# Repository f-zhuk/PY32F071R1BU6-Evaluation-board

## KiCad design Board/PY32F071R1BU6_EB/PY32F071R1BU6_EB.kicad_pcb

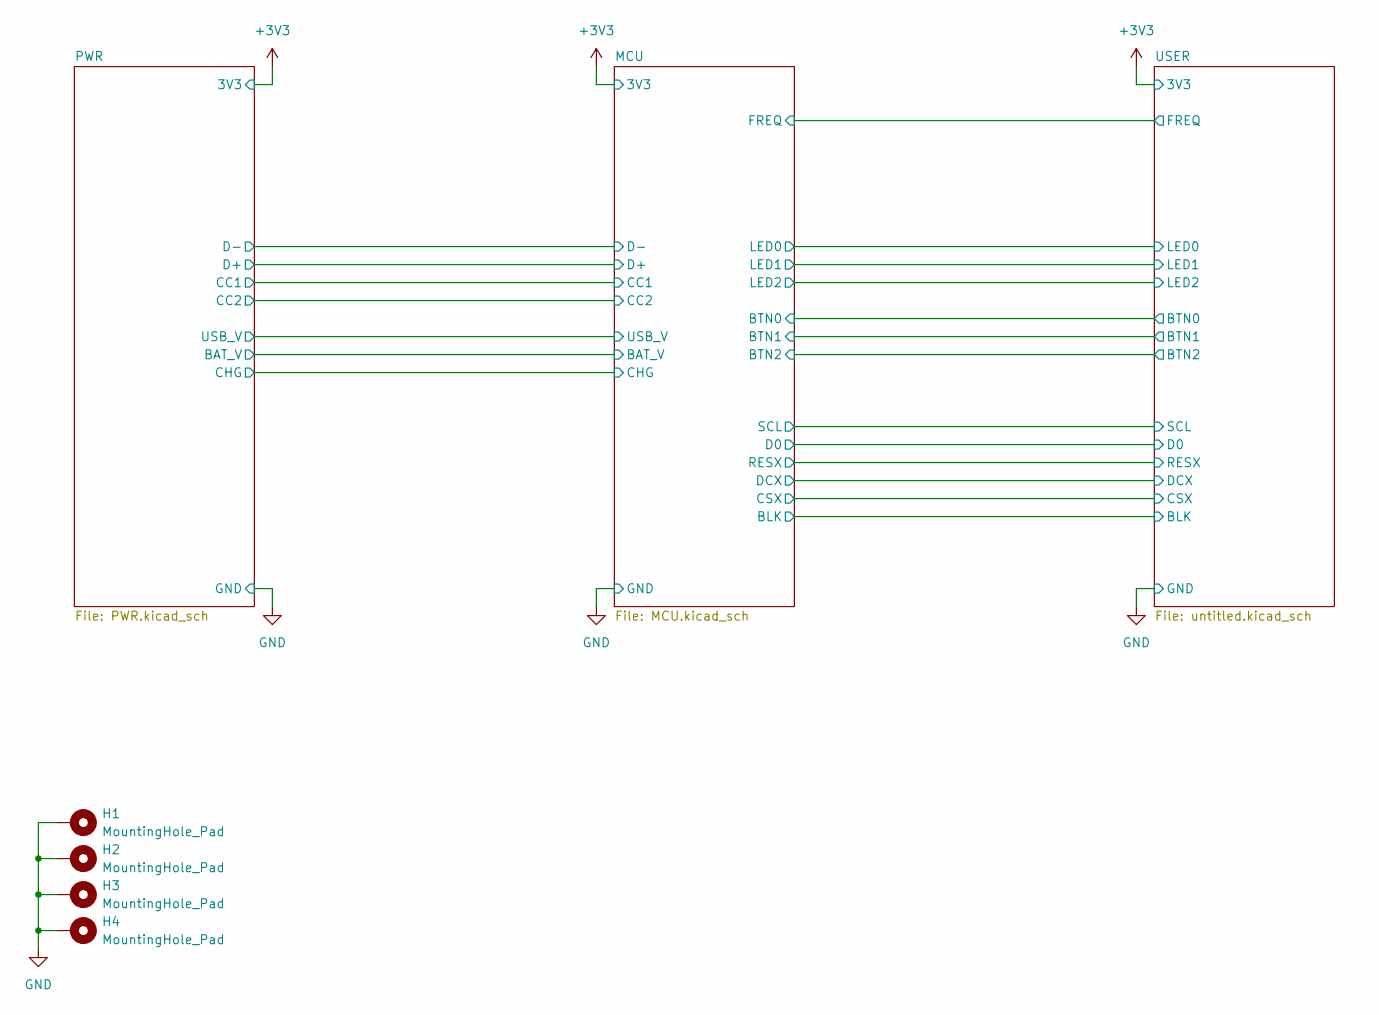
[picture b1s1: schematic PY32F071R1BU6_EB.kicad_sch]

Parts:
H1, H2, H3, H4: MountingHole_Pad; MountingHole_4.3mm_M4_Pad

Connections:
GND: H1.1, H2.1, H3.1, H4.1; also elsewhere on the board

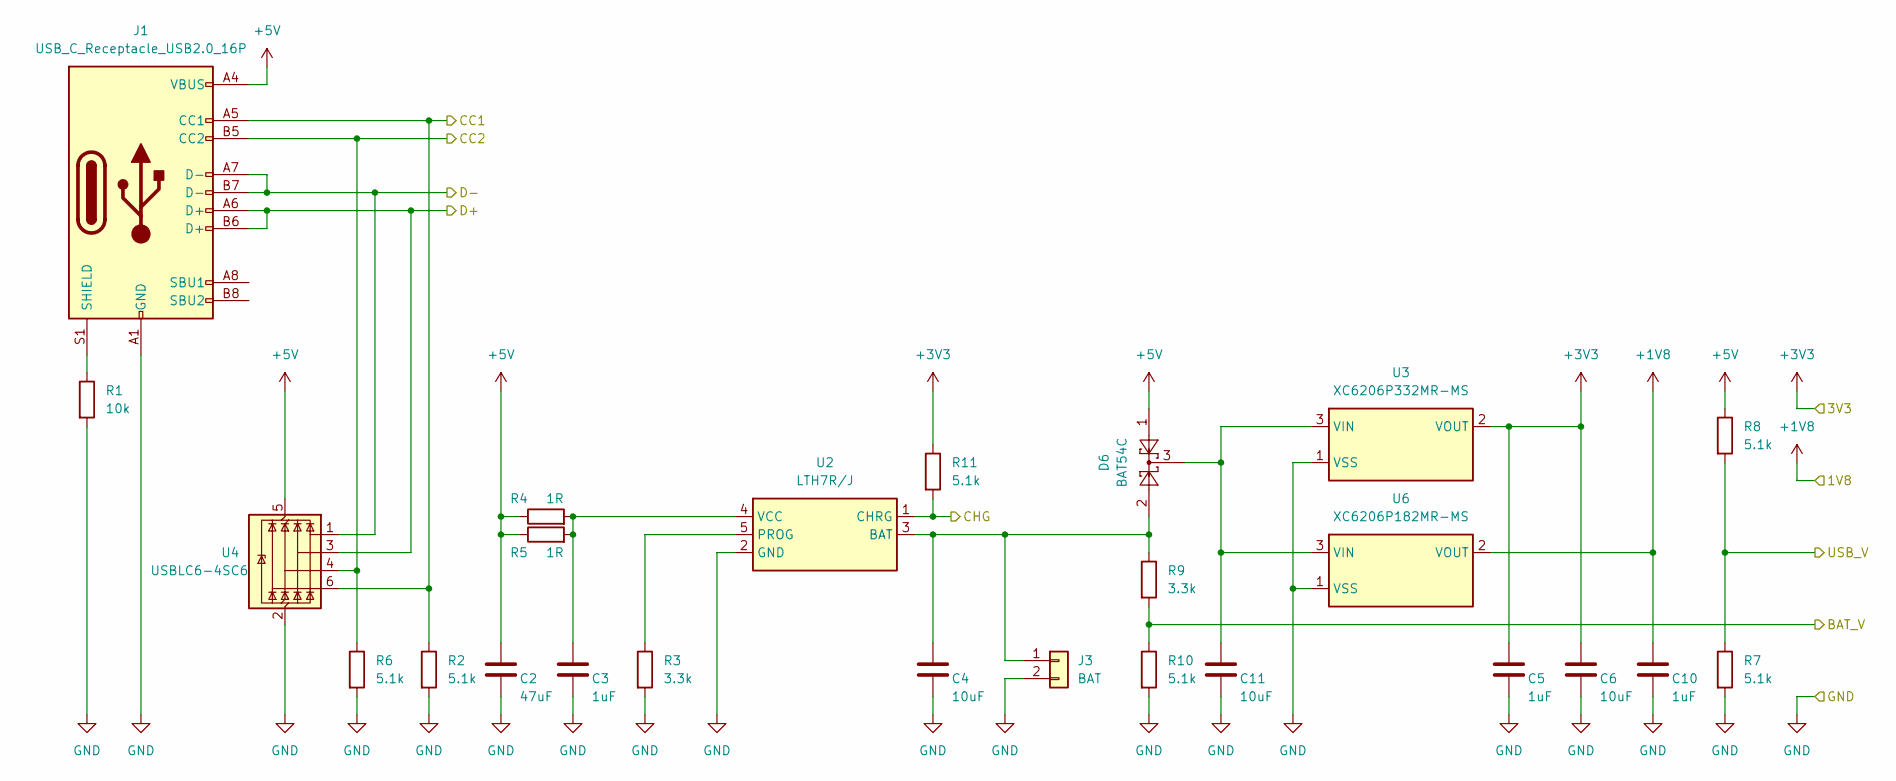
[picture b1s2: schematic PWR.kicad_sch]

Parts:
C2: 47uF; C_0805_2012Metric_Pad1.18x1.45mm_HandSolder; Voltage 10V
C3, C5, C10: 1uF; C_0603_1608Metric_Pad1.08x0.95mm_HandSolder; Voltage 10V
C4, C6, C11: 10uF; C_0603_1608Metric_Pad1.08x0.95mm_HandSolder; Voltage 10V
D6: BAT54C; SOT-23-3
J1: USB_C_Receptacle_USB2.0_16P; USB_C_Receptacle_HCTL_HC-TYPE-C-16P-01A
J3: BAT; PinHeader_1x02_P2.54mm_Vertical
R1: 10k; R_0603_1608Metric_Pad0.98x0.95mm_HandSolder
R2, R6, R7, R8, R10, R11: 5.1k; R_0603_1608Metric_Pad0.98x0.95mm_HandSolder
R3, R9: 3.3k; R_0603_1608Metric_Pad0.98x0.95mm_HandSolder
R4, R5: 1R; R_0603_1608Metric_Pad0.98x0.95mm_HandSolder
U2: LTH7R/J; SOT-23-5
U3: XC6206P332MR-MS; SOT-23-3
U4: USBLC6-4SC6; SOT-23-6
U6: XC6206P182MR-MS; SOT-23-3

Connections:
+1V8: C10.1, U6.2 (VOUT)
+3V3: C5.1, C6.1, R11.1, U3.2 (VOUT); also elsewhere on the board
+5V: C2.1, D6.1, J1.A4 (VBUS), J1.A9 (VBUS), J1.B4 (VBUS), J1.B9 (VBUS), R4.1, R5.1, R8.1, U4.5 (VBUS); also elsewhere on the board
/MCU/BAT_V: R9.2, R10.1; also elsewhere on the board
/MCU/CC1: J1.A5 (CC1), R2.1, U4.6 (I/O4); also elsewhere on the board
/MCU/CC2: J1.B5 (CC2), R6.1, U4.4 (I/O3); also elsewhere on the board
/MCU/CHG: R11.2, U2.1 (CHRG); also elsewhere on the board
/MCU/D+: J1.A6 (D+), J1.B6 (D+), U4.3 (I/O2); also elsewhere on the board
/MCU/D-: J1.A7 (D-), J1.B7 (D-), U4.1 (I/O1); also elsewhere on the board
/MCU/USB_V: R7.1, R8.2; also elsewhere on the board
GND: C2.2, C3.2, C4.2, C5.2, C6.2, C10.2, C11.2, J1.A1 (GND), J1.A12 (GND), J1.B1 (GND), J1.B12 (GND), J3.2, R1.2, R2.2, R3.2, R6.2, R7.2, R10.2, U2.2 (GND), U3.1 (VSS), U4.2 (GND), U6.1 (VSS); also elsewhere on the board
unnamed: J1.S1 (SHIELD), R1.1
unnamed: C4.1, D6.2, J3.1, R9.1, U2.3 (BAT)
unnamed: R3.1, U2.5 (PROG)
unnamed: C3.1, R4.2, R5.2, U2.4 (VCC)
unnamed: C11.1, D6.3, U3.3 (VIN), U6.3 (VIN)

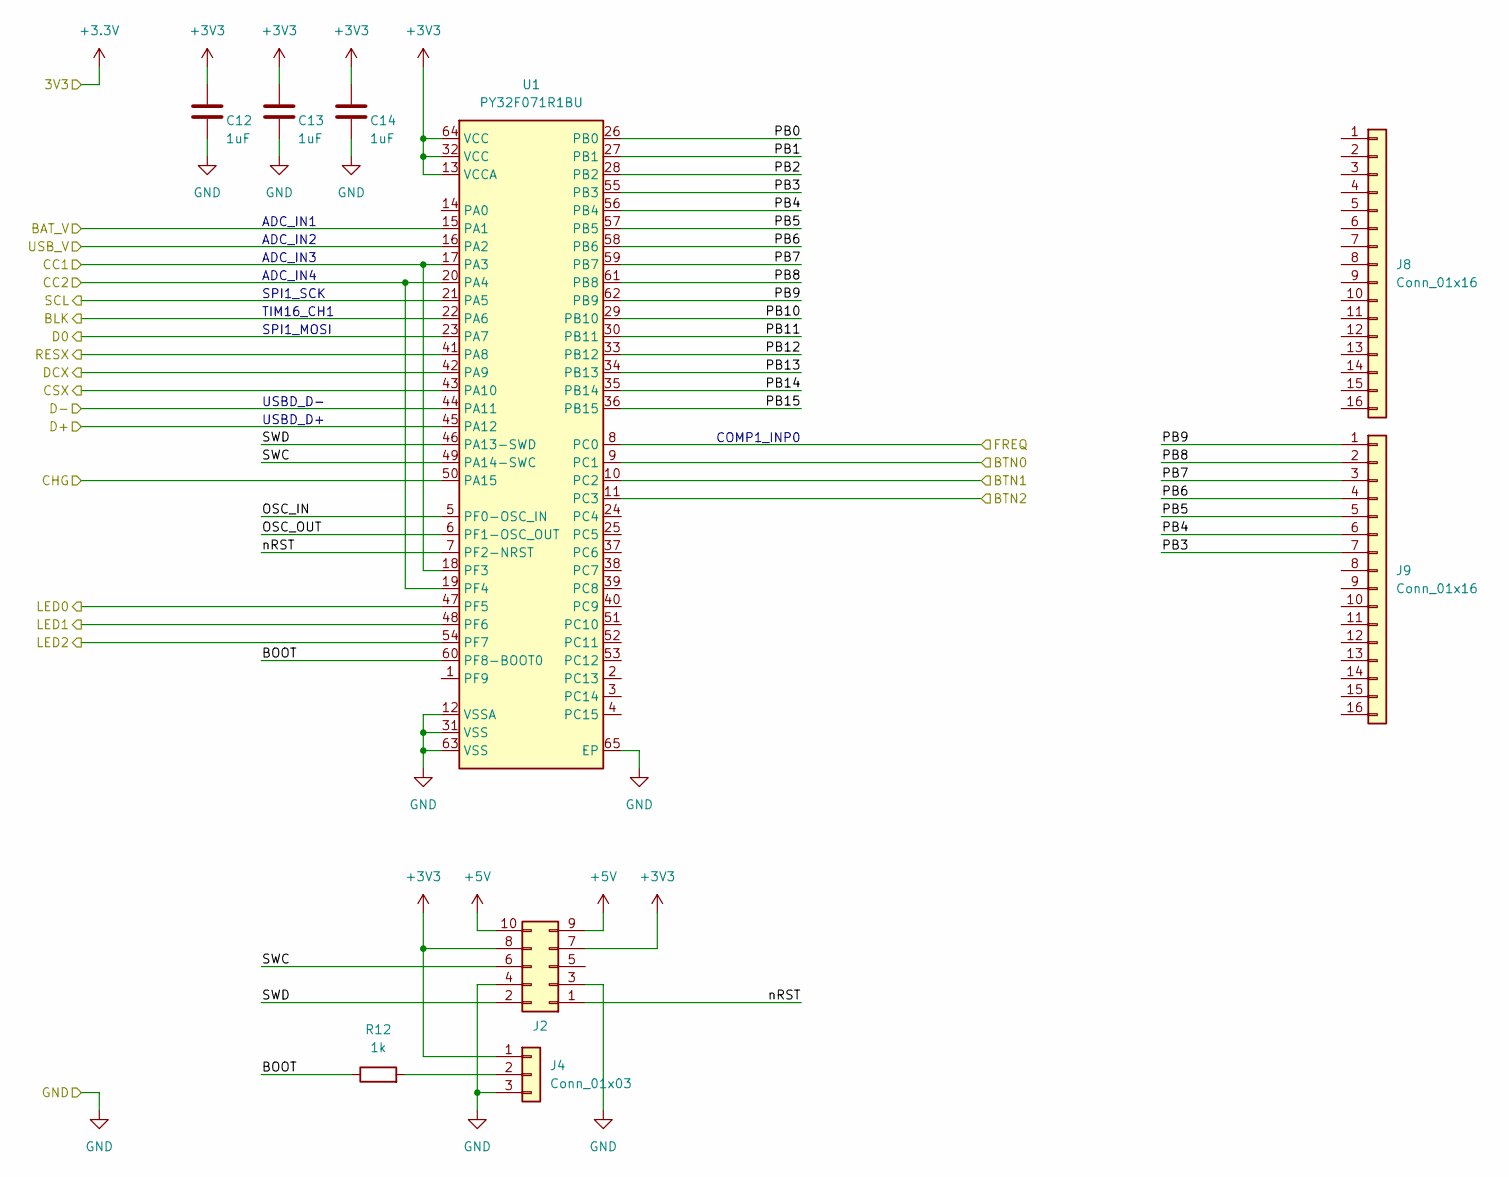
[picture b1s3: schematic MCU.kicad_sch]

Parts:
C12, C13, C14: 1uF; C_0603_1608Metric_Pad1.08x0.95mm_HandSolder; Voltage 10V
J2: Conn_02x05_Odd_Even; IDC-Header_2x05_P2.54mm_Vertical
J4: Conn_01x03; PinHeader_1x03_P2.54mm_Vertical
J8, J9: Conn_01x16; PinHeader_1x16_P2.54mm_Vertical
R12: 1k; R_0603_1608Metric_Pad0.98x0.95mm_HandSolder
U1: PY32F071R1BU; QFN-64-1EP_8x8mm_P0.4mm_EP6.5x6.5mm

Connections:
+3V3: C12.1, C13.1, C14.1, J2.7, J2.8, J4.1, U1.13 (VCCA), U1.32 (VCC), U1.64 (VCC); also elsewhere on the board
+5V: J2.9, J2.10; also elsewhere on the board
/MCU/BAT_V: U1.15 (PA1); also elsewhere on the board
/MCU/BLK: U1.22 (PA6); also elsewhere on the board
/MCU/BOOT: R12.1, U1.60 (PF8-BOOT0)
/MCU/BTN0: U1.9 (PC1); also elsewhere on the board
/MCU/BTN1: U1.10 (PC2); also elsewhere on the board
/MCU/BTN2: U1.11 (PC3); also elsewhere on the board
/MCU/CC1: U1.17 (PA3), U1.18 (PF3); also elsewhere on the board
/MCU/CC2: U1.19 (PF4), U1.20 (PA4); also elsewhere on the board
/MCU/CHG: U1.50 (PA15); also elsewhere on the board
/MCU/CSX: U1.43 (PA10); also elsewhere on the board
/MCU/D0: U1.23 (PA7); also elsewhere on the board
/MCU/D+: U1.45 (PA12); also elsewhere on the board
/MCU/D-: U1.44 (PA11); also elsewhere on the board
/MCU/DCX: U1.42 (PA9); also elsewhere on the board
/MCU/FREQ: U1.8 (PC0); also elsewhere on the board
/MCU/LED0: U1.47 (PF5); also elsewhere on the board
/MCU/LED1: U1.48 (PF6); also elsewhere on the board
/MCU/LED2: U1.54 (PF7); also elsewhere on the board
/MCU/OSC_IN: U1.5 (PF0-OSC_IN)
/MCU/OSC_OUT: U1.6 (PF1-OSC_OUT)
/MCU/PB0: U1.26 (PB0)
/MCU/PB1: U1.27 (PB1)
/MCU/PB2: U1.28 (PB2)
/MCU/PB3: J9.7, U1.55 (PB3)
/MCU/PB4: J9.6, U1.56 (PB4)
/MCU/PB5: J9.5, U1.57 (PB5)
/MCU/PB6: J9.4, U1.58 (PB6)
/MCU/PB7: J9.3, U1.59 (PB7)
/MCU/PB8: J9.2, U1.61 (PB8)
/MCU/PB9: J9.1, U1.62 (PB9)
/MCU/PB10: U1.29 (PB10)
/MCU/PB11: U1.30 (PB11)
/MCU/PB12: U1.33 (PB12)
/MCU/PB13: U1.34 (PB13)
/MCU/PB14: U1.35 (PB14)
/MCU/PB15: U1.36 (PB15)
/MCU/RESX: U1.41 (PA8); also elsewhere on the board
/MCU/SCL: U1.21 (PA5); also elsewhere on the board
/MCU/SWC: J2.6, U1.49 (PA14-SWC)
/MCU/SWD: J2.2, U1.46 (PA13-SWD)
/MCU/USB_V: U1.16 (PA2); also elsewhere on the board
/MCU/nRST: J2.1, U1.7 (PF2-NRST)
GND: C12.2, C13.2, C14.2, J2.3, J2.4, J4.3, U1.12 (VSSA), U1.31 (VSS), U1.63 (VSS), U1.65 (EP); also elsewhere on the board
unnamed: J4.2, R12.2

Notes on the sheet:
ADC_IN1
SPI1_SCK
USBD_D-
SPI1_MOSI
ADC_IN2
COMP1_INP0
TIM16_CH1
USBD_D+
ADC_IN3
ADC_IN4

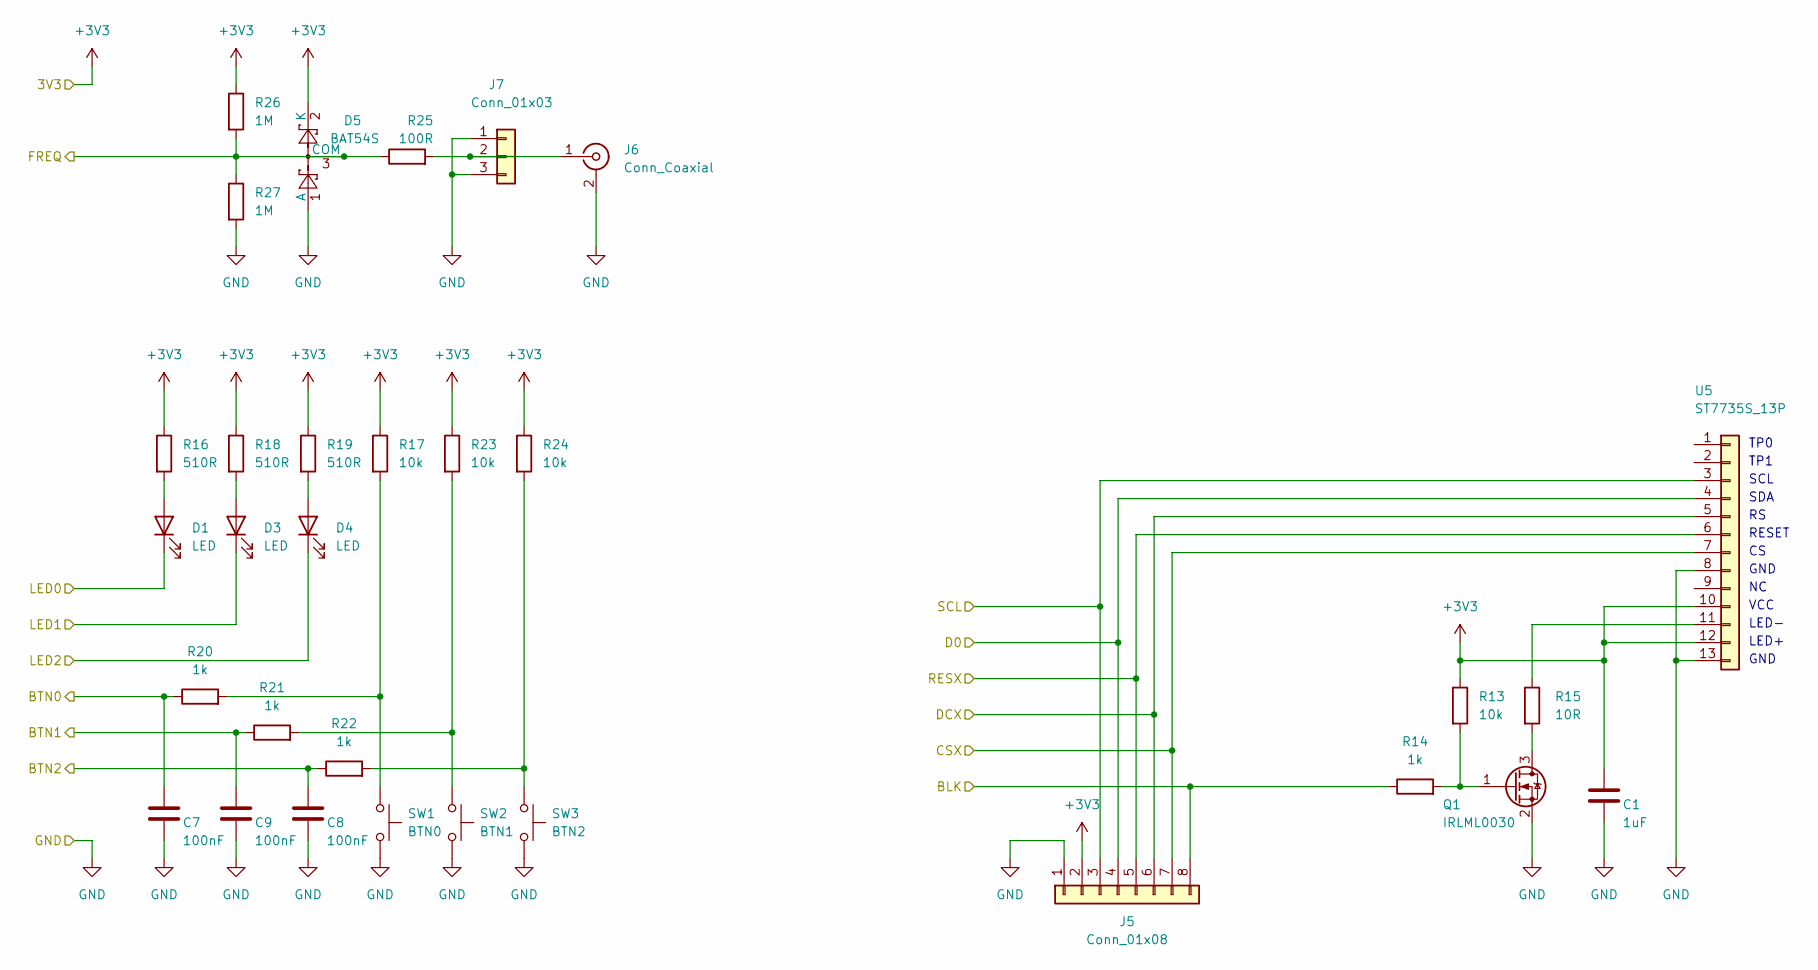
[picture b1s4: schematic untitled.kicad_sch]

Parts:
C1: 1uF; C_0603_1608Metric_Pad1.08x0.95mm_HandSolder; Voltage 10V
C7, C8, C9: 100nF; C_0603_1608Metric_Pad1.08x0.95mm_HandSolder; Voltage 10V
D1, D3, D4: LED; LED_0603_1608Metric
D5: BAT54S; SOT-23-3
J5: Conn_01x08; PinSocket_1x08_P2.54mm_Vertical
J6: Conn_Coaxial; U.FL_Hirose_U.FL-R-SMT-1_Vertical
J7: Conn_01x03; PinHeader_1x03_P2.54mm_Vertical
Q1: IRLML0030; SOT-23
R13, R17, R23, R24: 10k; R_0603_1608Metric_Pad0.98x0.95mm_HandSolder
R14, R20, R21, R22: 1k; R_0603_1608Metric_Pad0.98x0.95mm_HandSolder
R15: 10R; R_0603_1608Metric_Pad0.98x0.95mm_HandSolder
R16, R18, R19: 510R; R_0603_1608Metric_Pad0.98x0.95mm_HandSolder
R25: 100R; R_0603_1608Metric_Pad0.98x0.95mm_HandSolder
R26, R27: 1M; R_0603_1608Metric_Pad0.98x0.95mm_HandSolder
SW1: BTN0; SW_SPST_CK_PTS641
SW2: BTN1; SW_SPST_CK_PTS641
SW3: BTN2; SW_SPST_CK_PTS641
U5: ST7735S_13P; ST7735S_13P_0.96IN_80X160

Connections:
+3V3: C1.1, D5.2 (K), J5.2, R13.1, R16.1, R17.1, R18.1, R19.1, R23.1, R24.1, R26.1, U5.10, U5.12; also elsewhere on the board
/MCU/BLK: J5.8, R14.1; also elsewhere on the board
/MCU/BTN0: C7.1, R20.1; also elsewhere on the board
/MCU/BTN1: C9.1, R21.1; also elsewhere on the board
/MCU/BTN2: C8.1, R22.1; also elsewhere on the board
/MCU/CSX: J5.7, U5.7; also elsewhere on the board
/MCU/D0: J5.4, U5.4; also elsewhere on the board
/MCU/DCX: J5.6, U5.5; also elsewhere on the board
/MCU/FREQ: D5.3 (COM), R25.1, R26.2, R27.1; also elsewhere on the board
/MCU/LED0: D1.1 (K); also elsewhere on the board
/MCU/LED1: D3.1 (K); also elsewhere on the board
/MCU/LED2: D4.1 (K); also elsewhere on the board
/MCU/RESX: J5.5, U5.6; also elsewhere on the board
/MCU/SCL: J5.3, U5.3; also elsewhere on the board
GND: C1.2, C7.2, C8.2, C9.2, D5.1 (A), J5.1, J6.2 (Ext), J7.1, J7.3, Q1.2 (S), R27.2, SW1.2, SW2.2, SW3.2, U5.8, U5.13; also elsewhere on the board
unnamed: D1.2 (A), R16.2
unnamed: D3.2 (A), R18.2
unnamed: D4.2 (A), R19.2
unnamed: J6.1 (In), J7.2, R25.2
unnamed: Q1.3 (D), R15.2
unnamed: Q1.1 (G), R13.2, R14.2
unnamed: R17.2, R20.2, SW1.1
unnamed: R21.2, R23.2, SW2.1
unnamed: R22.2, R24.2, SW3.1
unnamed: R15.1, U5.11

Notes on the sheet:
LED+
SDA
SCL
RESET
LED-
TP1
TP0
VCC
GND

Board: 2 copper layers, 69 parts (18 on the bottom side), 51 nets, no tracks yet.

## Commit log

2024-09-15 Initial push
2024-09-15 Properly excluded local KiCAD backup files
2024-09-15 Added USB connector
2024-09-21 Kicad project was split in hierarchical sheets
2024-09-29 Power circuit prepared
2024-09-29 Display added to schematic
2024-10-06 Schematic updated
2024-10-06 Component placement started
